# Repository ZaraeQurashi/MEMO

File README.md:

# MEMO — Desktop Reminder Display

A compact, Wi-Fi desktop reminder and deadline tracker built with a custom PCB, Seeed Studio XIAO ESP32-C3, and a 128 × 64 OLED display.

## Overview

MEMO is a custom-built desktop reminder and information display designed to make tracking upcoming deadlines easier. Powered by the Seeed Studio XIAO ESP32-C3, it uses an OLED screen to display reminders, their due dates, and the time remaining until each deadline.

The device connects to Wi-Fi to retrieve the current time through Network Time Protocol (NTP), allowing it to calculate deadlines automatically. Three physical push buttons provide simple navigation and reminder controls, while an RGB LED communicates the urgency of each reminder through colour-coded notifications.

## Features

- Reminder Display: Displays individual reminders, their due dates, and completion status.
- Real-Time Clock: Connects to Wi-Fi and synchronizes the current time using NTP.
- Deadline Countdown: Calculates the time remaining until each reminder is due.
- OLED Interface: Displays the current date, time, selected reminder, and its status.
- Three-Button Navigation: Browse between reminders and mark them as completed.
- RGB Notifications: Uses different LED colours to indicate the urgency of reminders.
- Custom PCB: Designed in KiCad around the Seeed Studio XIAO ESP32-C3.

## Hardware

## Hardware

MEMO is built around the Seeed Studio XIAO ESP32-C3, which handles reminder calculations, Wi-Fi connectivity, display communication, and physical inputs.

### Components & Bill of Materials

All prices are in CAD and reflect the estimated component costs at the time of purchase.

| Component                          | Qty Used | Qty Purchased | Purpose                            | Supplier  | Cost       | Total  |
| ---------------------------------- | -------- | ------------- | ---------------------------------- | --------- | ---------- | ------ |
| Seeed Studio XIAO ESP32-C3         | 1        | 1             | Main microcontroller               | RobotShop | $8.50      | $8.50  |
| 0.96" Grove OLED Display (SSD1315) | 1        | 1             | Displays reminders and information | RobotShop | $7.86      | $7.86  |
| Triple Output RGB LED              | 1        | 1             | Visual status notifications        | RobotShop | $3.29      | $3.29  |
| 330 Ω Resistors                    | 3        | 1 (20-pack)   | Limit RGB LED current              | RobotShop | $1.79/pack | $1.79  |
| Mini Push Button Switches          | 3        | 3             | Reminder navigation and selection  | RobotShop | $0.71      | $2.13  |
| Custom PCB                         | 1        | 1             | Connects all components            | JLCPCB    | $5.58      | $5.58  |
| Total                              | 10       |               |                                    |           |            | $29.15 |

The resistor purchase includes a 20-piece pack, of which three resistors are used on the PCB. Shipping is excluded from the total.

### Purchase Links

- [PCB Board — JLCPCB](https://cart.jlcpcb.com/quote?stencilLayer=2\&stencilWidth=100\&stencilLength=100\&stencilCounts=5\&plateType=1\&utm_source=chatgpt.com)
- [RGB LED — RobotShop](https://ca.robotshop.com/products/sfe-triple-output-led-rgb?utm_source=chatgpt.com)
- [330 Ω Resistors — RobotShop](https://ca.robotshop.com/products/resistor-330-ohm-1-4-watt-pth-20pk?utm_source=chatgpt.com)
- [Mini Push Button Switches — RobotShop](https://ca.robotshop.com/products/sfe-mini-push-button-switch?utm_source=chatgpt.com)
- [Seeed Studio XIAO ESP32-C3 — RobotShop](https://ca.robotshop.com/products/seeedstudio-xiao-esp32c3-tiny-mcu-w-wi-fi-ble?utm_source=chatgpt.com)
- [Grove OLED Display — RobotShop](https://ca.robotshop.com/products/seeedstudio-grove-oled-yellow-blue-display-096-in-ssd1315-v10?utm_source=chatgpt.com)

## PCB Design

The schematic and PCB were designed using KiCad. The layout was arranged to keep the microcontroller, OLED connector, buttons, RGB LED, and current-limiting resistors organized within a compact board.

The circuit uses the XIAO ESP32-C3's GPIO pins to control the three LED channels and read the push buttons. The OLED communicates with the microcontroller over I²C.

Three 330 Ω resistors are included to limit the current flowing through the RGB LED's individual colour channels. The push buttons use the microcontroller's internal pull-up resistors, allowing them to connect directly between their GPIO pins and GND.

### Pin Configuration

| Component | Function | XIAO Pin | GPIO |
|---|---|---|---|
| OLED | SDA | D5 | GPIO7 |
| OLED | SCL | D4 | GPIO6 |
| RGB LED | Red | D1 | GPIO3 |
| RGB LED | Green | D2 | GPIO4 |
| RGB LED | Blue | D3 | GPIO5 |
| UP Button | Input | D6 | GPIO21 |
| DOWN Button | Input | D7 | GPIO20 |
| SELECT Button | Input | D10 | GPIO10 |

### PCB Images

## Controls

MEMO uses three physical push buttons to navigate through the reminder list.

| Button | Function |
|---|---|
| UP | Move to the previous reminder |
| DOWN | Move to the next reminder |
| SELECT | Mark the selected reminder as completed or incomplete |

The reminder list loops around when navigating. For example, pressing UP while viewing the first reminder takes you to the last reminder, while pressing DOWN on the last reminder returns to the first.

The buttons use `INPUT_PULLUP`, meaning that their normal state is HIGH and their pressed state is LOW. A debounce interval is also included to prevent a single physical press from being registered multiple times.

## RGB LED Status Indicators

The RGB LED provides a quick visual indication of the selected reminder's status.

| LED Colour | Meaning |
|---|---|
| Green | More than 24 hours remaining |
| Blue | Less than 24 hours remaining |
| Red | Reminder is overdue |
| Off | Reminder has been completed |

The LED also displays blue while the device is waiting for a valid time synchronization.

## Firmware

The firmware was written in C++ using Arduino IDE for the Seeed Studio XIAO ESP32-C3.

### Libraries

The following libraries and built-in ESP32 features are used:

| Library | Purpose |
|---|---|
| `WiFi.h` | Connects the ESP32-C3 to Wi-Fi |
| `Wire.h` | Handles I²C communication with the OLED |
| `time.h` | Provides time conversion and deadline calculations |
| `Adafruit_GFX` | Provides graphics and text functionality |
| `Adafruit_SSD1306` | Controls the OLED display |

### How It Works

**1. Reminder Storage**

Reminders are stored in a C++ structure containing:
- Title
- Year
- Month
- Day
- Hour
- Minute
- Completion status

An array stores multiple reminders, while `selectedReminder` tracks which entry is currently displayed.

**2. Time Synchronization**

When MEMO starts, it attempts to connect to Wi-Fi. After successfully connecting, it retrieves the current time from an NTP server.

The timezone is configured for Eastern Time, including automatic daylight saving time adjustments.

**3. Deadline Calculations**

The firmware converts each reminder's date and time into a timestamp using `mktime()`. It then compares this value with the current time using `difftime()`.

Based on the difference, MEMO determines whether a reminder is overdue, due within 24 hours, or due further in the future.

**4. OLED Updates**

The `updateDisplay()` function refreshes the OLED with the current date, time, selected reminder, and its deadline status.

The display refreshes approximately once every second using `millis()`.

**5. Button Interaction**

The main `loop()` continuously checks for button presses. Depending on the input, it changes the selected reminder or toggles its completion status.

**6. LED Notifications**

The `setLED()` function controls the three RGB channels independently, allowing the firmware to display the appropriate colour for each reminder status.

## Setting Up the Firmware

To upload the firmware to your own MEMO board:

1. Install [Arduino IDE](https://www.arduino.cc/en/software).
2. Install the ESP32 board package and select the Seeed Studio XIAO ESP32-C3.
3. Install the Adafruit GFX and Adafruit SSD1306 libraries through the Arduino Library Manager.
4. Open the MEMO firmware file.
5. Enter your Wi-Fi credentials in the following section:

```cpp
const char* ssid = "YOUR_WIFI_NAME";
const char* password = "YOUR_WIFI_PASSWORD";
```

6. Check that the GPIO definitions match your PCB connections.
7. Connect the XIAO ESP32-C3 to your computer and select the correct port.
8. Compile and upload the firmware.

## Current Limitations and Future Improvements

This is the first firmware version of MEMO, so there are a few features that could be improved in future updates:

- **Hardcoded Reminders:** Reminders currently need to be edited directly in the source code and uploaded again.
- **No Persistent Storage:** Completion statuses reset when the device restarts.
- **Wi-Fi Dependency:** A network connection is required to synchronize the clock and obtain accurate time.
- **Limited Reminder Management:** The current buttons allow users to browse and complete reminders, but not create or edit them directly on the device.

Potential improvements for future versions include:

- Adding the ability to create, edit, and delete reminders directly on the device.
- Saving reminder data and completion statuses using ESP32 non-volatile storage.
- Improving the OLED interface with icons, better layouts, and additional information.
- Adding more notification options and customizable LED behaviour.
- Improving offline functionality by retaining the last synchronized time.

## Summary

MEMO is a custom-built desktop reminder system designed to make tracking upcoming deadlines and events easier. Powered by the Seeed Studio XIAO ESP32-C3, it uses an OLED display to show reminders, three push buttons for navigation and selection, and an RGB LED to communicate reminder statuses. The project combines custom PCB design in KiCad with firmware developed in Arduino IDE, including Wi-Fi connectivity and automatic time synchronization.

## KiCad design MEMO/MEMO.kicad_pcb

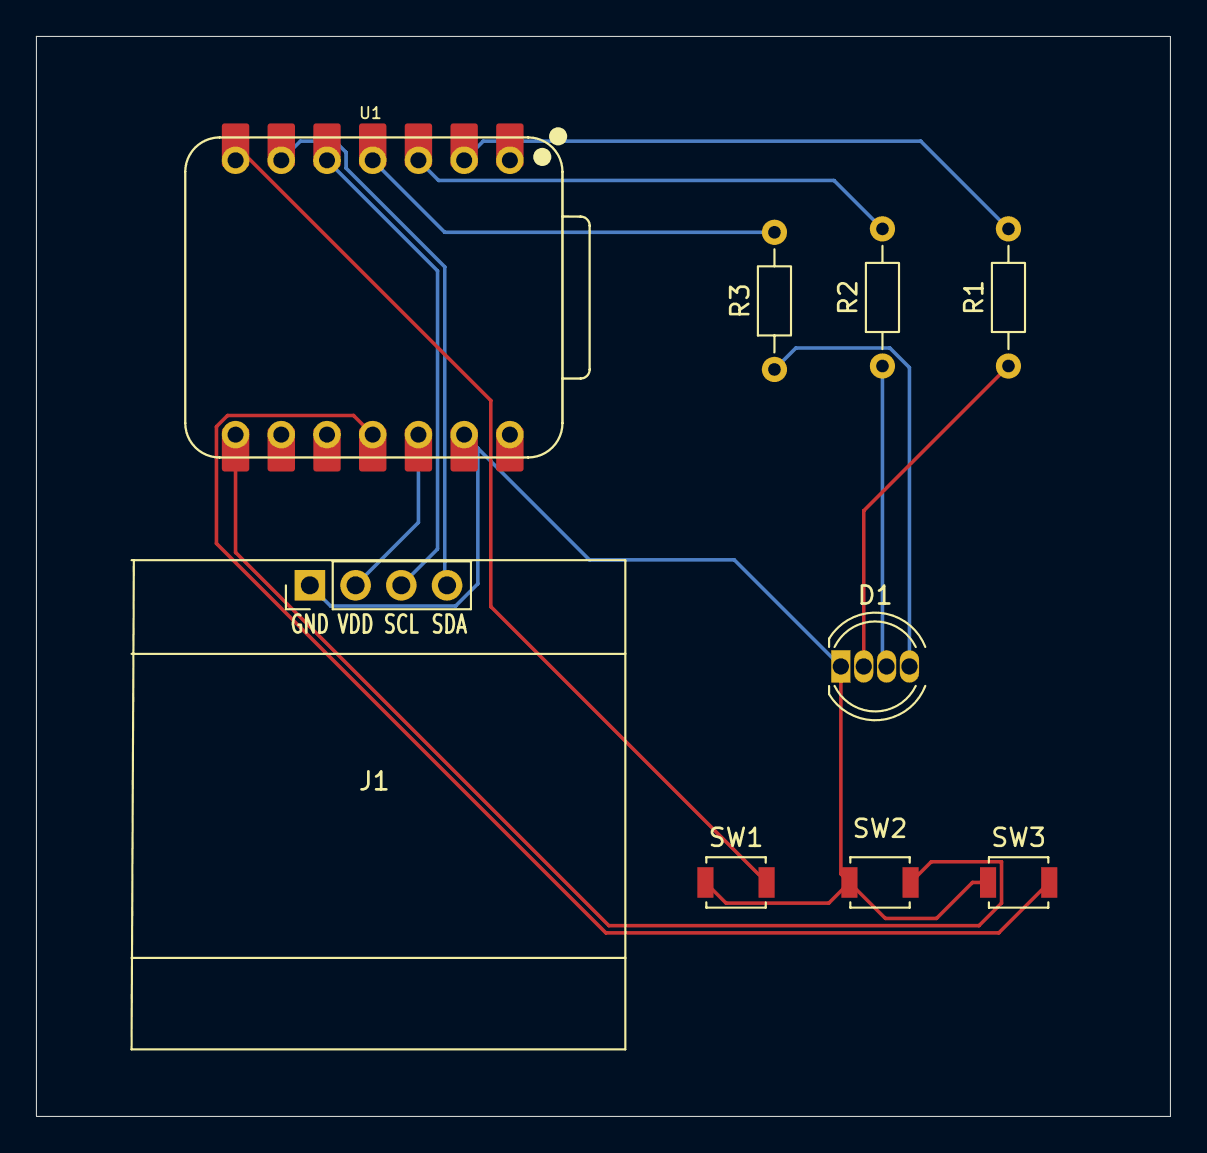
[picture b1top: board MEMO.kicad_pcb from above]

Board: 2 copper layers, 63.0 x 60.0 mm, 9 parts (0 on the bottom side), 13 nets.

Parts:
D1: LED_ARGB; LED_D5.0mm-4_RGB
J1: Conn_01x04_Pin; Display_128x64_096_I2C
R1, R2, R3: 330; R_Axial_DIN0204_L3.6mm_D1.6mm_P7.62mm_Horizontal
SW1, SW2, SW3: SW_Push; SW_SPST_B3U-1000P
U1: XIAO-ESP32-C3-SMD; XIAO-ESP32-C6-DIP

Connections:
+3.3V: J1.2, U1.12 (3V3_OUT)
/BLUE: R3.2, U1.4 (D3)
/DOWN: SW2.2, U1.8 (D7)
/GREEN: R2.2, U1.3 (D2)
/RED: R1.2, U1.2 (D1)
/SCL: J1.3, U1.5 (D4)
/SDA: J1.4, U1.6 (D5)
/SELECT: SW3.2, U1.11 (D10)
/UP: SW1.2, U1.7 (D6)
GND: D1.1 (A), J1.1, SW1.1, SW2.1, SW3.1, U1.13 (GND)
unnamed: D1.4 (BK), R3.1
unnamed: D1.3 (GK), R2.1
unnamed: D1.2 (RK), R1.1
